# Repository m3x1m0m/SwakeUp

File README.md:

# SwakeUp
A device to wake you up in Sweden (because it is so dark in the winter).

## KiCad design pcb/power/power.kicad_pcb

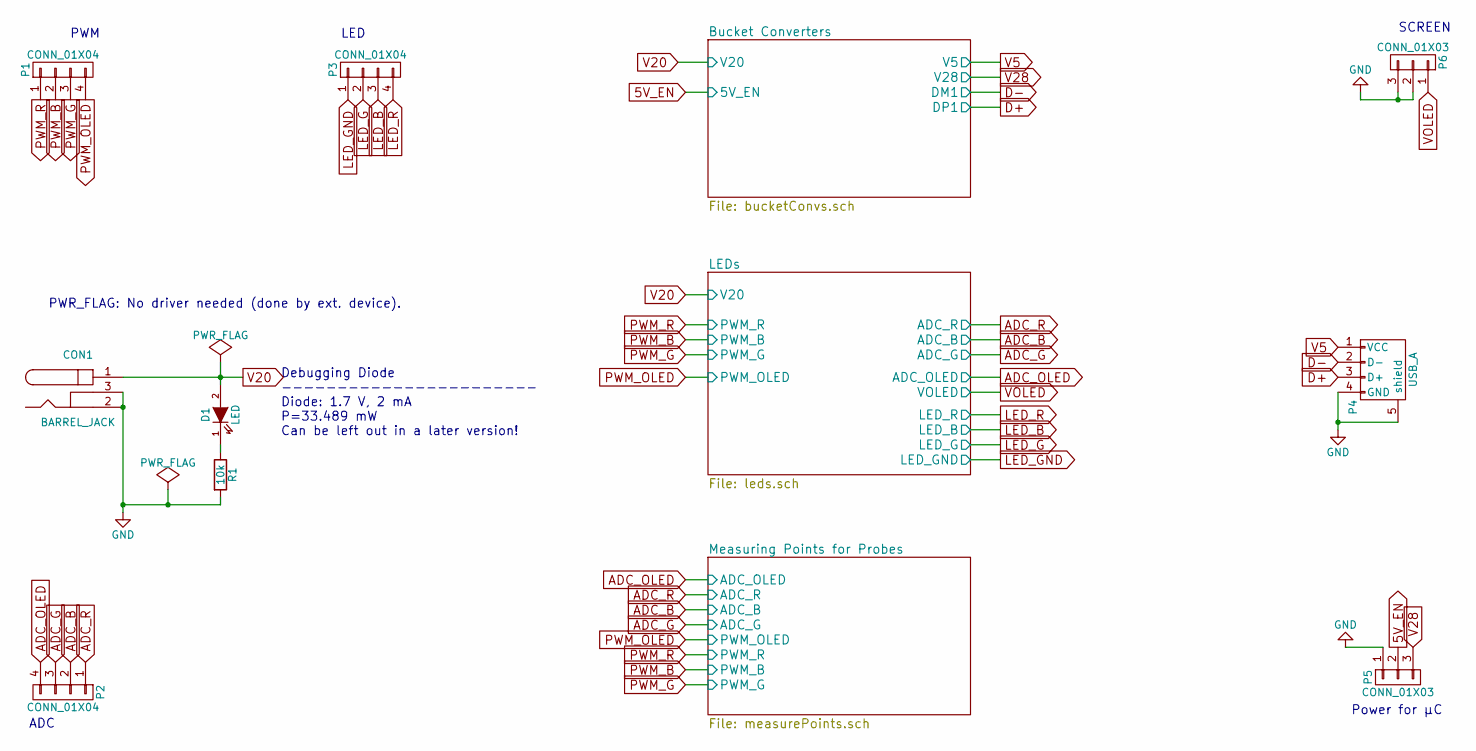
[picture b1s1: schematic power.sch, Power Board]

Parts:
CON1: BARREL_JACK; PJ-047BH_BARREL_JACK; Digikey CP-047BH-ND
D1: LED; LED_0603; Digikey 475-3118-1-ND
P1, P2: CONN_01X04; ESQ-104-12-G-S-LL
P3: CONN_01X04; LED_CONN_1.25_PITCH
P4: USB_A; Digikey 609-1045-ND
P5, P6: CONN_01X03; ESQ-103-12-G-S-LL
R1: 10k; R_0603_HandSoldering_Same_As_C; Digikey 311-10.0KHRCT-ND

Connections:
5V_EN: P5.2; also elsewhere on the board
ADC_B: P2.2; also elsewhere on the board
ADC_G: P2.3; also elsewhere on the board
ADC_OLED: P2.4; also elsewhere on the board
ADC_R: P2.1; also elsewhere on the board
D+: P4.3 (D+); also elsewhere on the board
D-: P4.2 (D-); also elsewhere on the board
LED_B: P3.2; also elsewhere on the board
LED_G: P3.3; also elsewhere on the board
LED_GND: CON1.2, CON1.3, P3.1, P4.4 (GND), P4.5 (shield), P5.1, P6.2, P6.3, R1.2; also elsewhere on the board
LED_R: P3.4; also elsewhere on the board
unnamed: D1.1 (K), R1.1
PWM_B: P1.2; also elsewhere on the board
PWM_G: P1.3; also elsewhere on the board
PWM_OLED: P1.4; also elsewhere on the board
PWM_R: P1.1; also elsewhere on the board
V5: P4.1 (VCC); also elsewhere on the board
V20: CON1.1, D1.2 (A); also elsewhere on the board
V28: P5.3; also elsewhere on the board
VOLED: P6.1; also elsewhere on the board

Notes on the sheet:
ADC
PWM
SCREEN
Debugging Diode ----------------------- Diode: 1.7 V, 2 mA P=33.489 mW Can be left out in a later version!
PWR_FLAG: No driver needed (done by ext. device).
Power for µC
LED

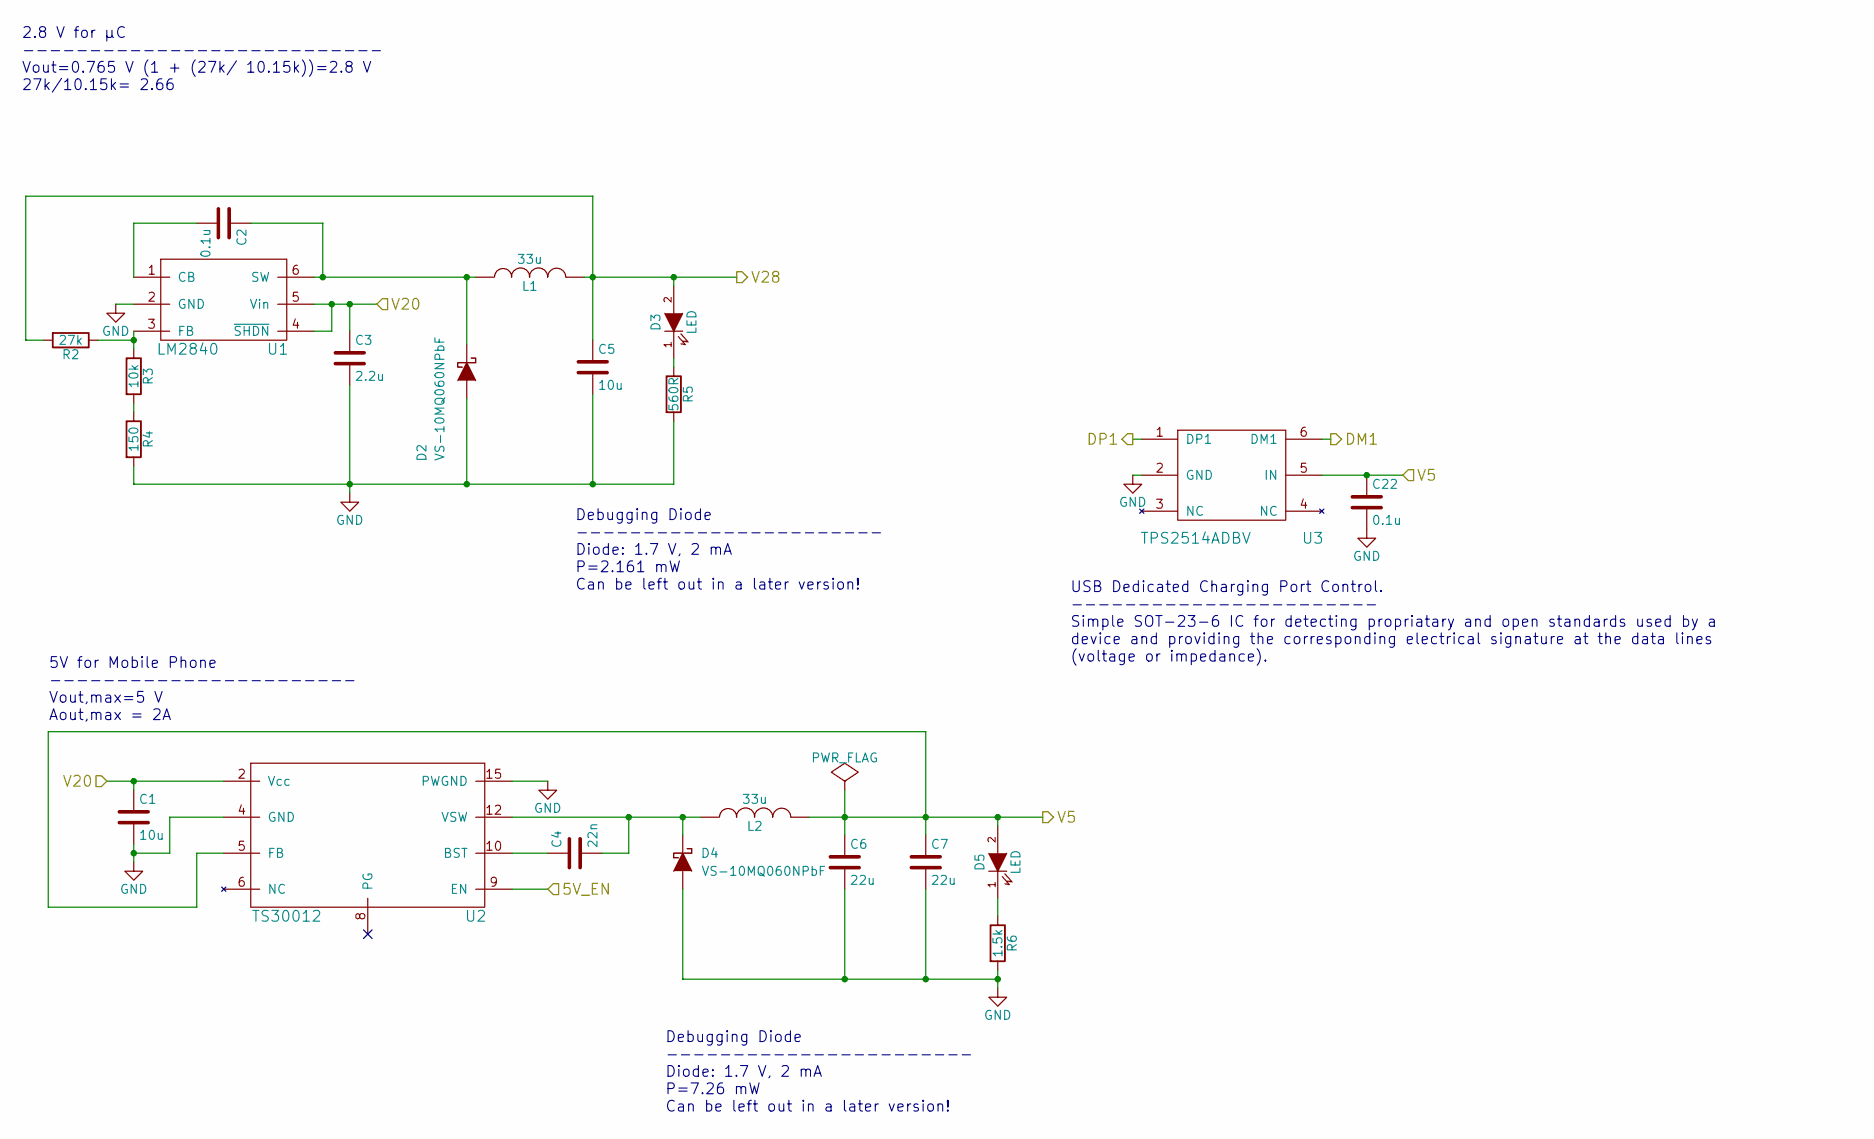
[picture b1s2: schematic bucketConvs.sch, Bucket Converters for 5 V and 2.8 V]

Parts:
C1, C5: 10u; C_0603_HandSoldering; Digikey 490-12323-1-ND
C2, C22: 0.1u; C_0603_HandSoldering; Digikey 311-1343-1-ND
C3: 2.2u; C_0603_HandSoldering; Digikey 490-7204-1-ND
C4: 22n; C_0603_HandSoldering; Digikey 445-8118-1-ND
C6, C7: 22u; C_0603_HandSoldering; Digikey 1276-1193-1-ND
D2, D4: VS-10MQ060NPbF; SMA_Handsoldering; Digikey 10MQ060NPBFCT-ND
D3, D5: LED; LED_0603; Digikey 475-3118-1-ND
L1, L2: 33u; Bourns_SRN3015; Digikey SRN3015-330MCT-ND
R2: 27k; R_0603_HandSoldering_Same_As_C; Digikey P27.0KHCT-ND
R3: 10k; R_0603_HandSoldering_Same_As_C; Digikey 311-10KGRCT-ND
R4: 150; R_0603_HandSoldering_Same_As_C; Digikey 311-150HRCT-ND
R5: 560R; R_0603_HandSoldering_Same_As_C; Digikey 311-560GRCT-ND
R6: 1.5k; R_0603_HandSoldering_Same_As_C; Digikey 311-1.5KGRCT-ND
U1: LM2840; SOT-23-6; Digikey LM2840XMK-ADJL/NOPBCT-ND
U2: TS30012; QFN-16-1EP_3x3mm_Pitch0.5mm; Digikey TS30012-M050QFNRCT-ND
U3: TPS2514ADBV; SOT-23-6; Digikey 296-40725-1-ND

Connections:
5V_EN: U2.9 (EN); also elsewhere on the board
D+: U3.1 (DP1); also elsewhere on the board
D-: U3.6 (DM1); also elsewhere on the board
LED_GND: C1.2, C3.2, C5.2, C6.2, C7.2, C22.2, D2.2 (A), D4.2 (A), R4.2, R5.2, R6.2, U1.2 (GND), U2.4 (GND), U2.14 (PWGND), U2.15 (PWGND), U3.2 (GND); also elsewhere on the board
unnamed: C2.1, D2.1 (K), L1.1, U1.6 (SW)
unnamed: C2.2, U1.1 (CB)
unnamed: C4.1, U2.10 (BST)
unnamed: C4.2, D4.1 (K), L2.1, U2.1 (VSW), U2.12 (VSW), U2.13 (VSW), U2.16 (VSW)
unnamed: D3.1 (K), R5.1
unnamed: D5.1 (K), R6.1
unnamed: R2.1, R3.1, U1.3 (FB)
unnamed: R3.2, R4.1
V5: C6.1, C7.1, C22.1, D5.2 (A), L2.2, U2.5 (FB), U3.5 (IN); also elsewhere on the board
V20: C1.1, C3.1, U1.4 (~SHDN), U1.5 (Vin), U2.2 (Vcc), U2.3 (Vcc), U2.11 (Vcc); also elsewhere on the board
V28: C5.1, D3.2 (A), L1.2, R2.2; also elsewhere on the board

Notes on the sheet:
2.8 V for µC --------------------------- Vout=0.765 V (1 + (27k/ 10.15k))=2.8 V 27k/10.15k= 2.66
Debugging Diode ----------------------- Diode: 1.7 V, 2 mA P=2.161 mW Can be left out in a later version!
Debugging Diode ----------------------- Diode: 1.7 V, 2 mA P=7.26 mW Can be left out in a later version!
5V for Mobile Phone ----------------------- Vout,max=5 V Aout,max = 2A
USB Dedicated Charging Port Control. ----------------------- Simple SOT-23-6 IC for detecting propriatary and open standards used by a device and providing the corresponding electrical signature at the data lines (voltage or impedance).

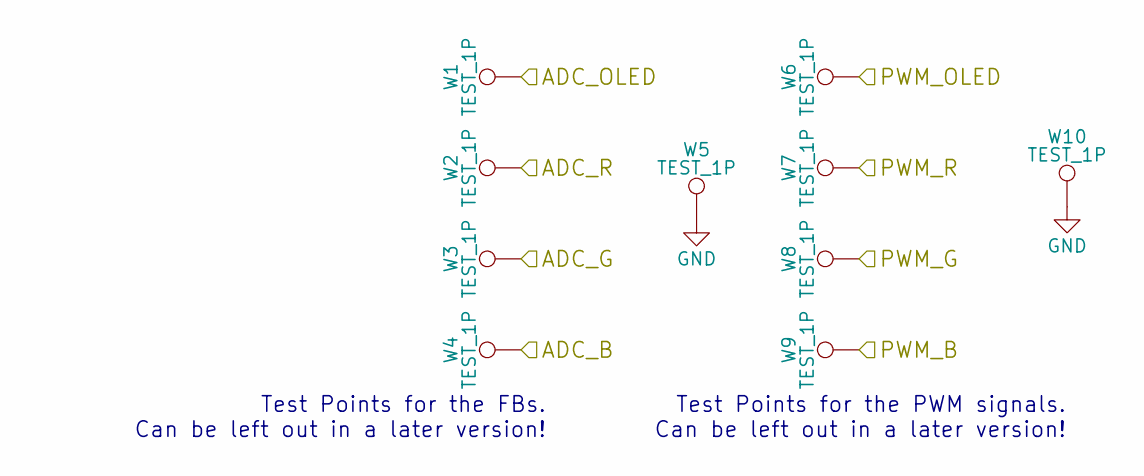
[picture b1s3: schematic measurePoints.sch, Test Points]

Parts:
W1, W2, W3, W4, W6, W7, W8, W9: TEST_1P; TP_PROBE
W5, W10: TEST_1P; GND_PROBE

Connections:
ADC_B: W4.1; also elsewhere on the board
ADC_G: W3.1; also elsewhere on the board
ADC_OLED: W1.1; also elsewhere on the board
ADC_R: W2.1; also elsewhere on the board
LED_GND: W5.1, W10.1; also elsewhere on the board
PWM_B: W9.1; also elsewhere on the board
PWM_G: W8.1; also elsewhere on the board
PWM_OLED: W6.1; also elsewhere on the board
PWM_R: W7.1; also elsewhere on the board

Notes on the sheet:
Test Points for the FBs. Can be left out in a later version!
Test Points for the PWM signals. Can be left out in a later version!

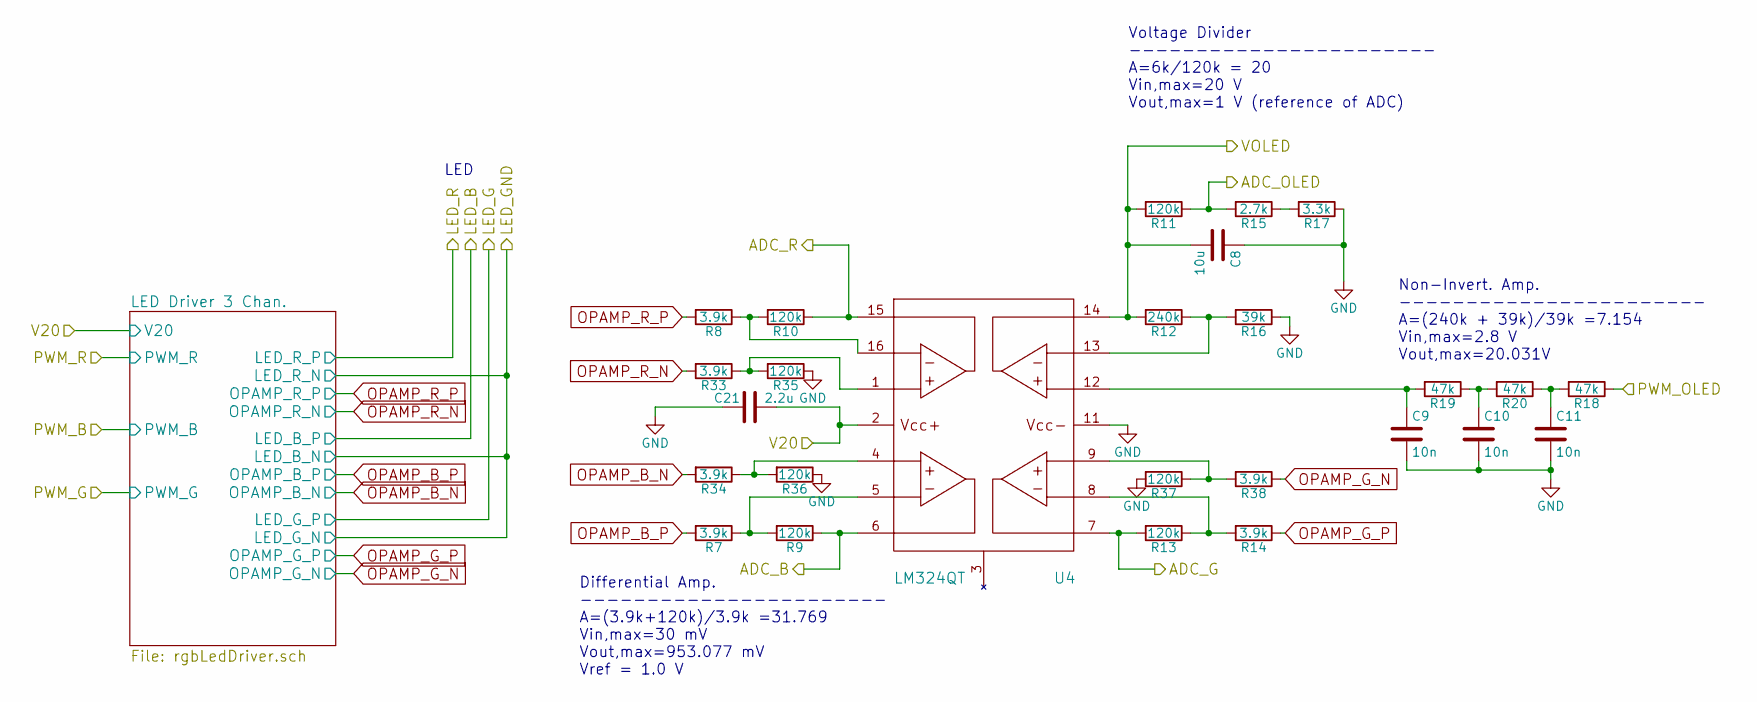
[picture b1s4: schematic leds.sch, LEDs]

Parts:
C8: 10u; C_0603_HandSoldering; Digikey 490-12323-1-ND
C9, C10, C11: 10n; C_0603_HandSoldering; Digikey 311-1085-1-ND
C21: 2.2u; C_0603_HandSoldering; Digikey 490-7204-1-ND
R7, R8, R14, R33, R34, R38: 3.9k; R_0603_HandSoldering_Same_As_C; Digikey 311-3.90KHRCT-ND
R9, R10, R11, R13, R35, R36, R37: 120k; R_0603_HandSoldering_Same_As_C; Digikey 311-120KHRCT-ND
R12: 240k; R_0603_HandSoldering_Same_As_C; Digikey 311-240KHRCT-ND
R15: 2.7k; R_0603_HandSoldering_Same_As_C; Digikey 311-2.70KHRCT-ND
R16: 39k; R_0603_HandSoldering_Same_As_C; Digikey 311-39.0KHRCT-ND
R17: 3.3k; R_0603_HandSoldering_Same_As_C; Digikey 311-3.30KHRCT-ND
R18, R19, R20: 47k; R_0603_HandSoldering_Same_As_C; Digikey 311-47.0KHRCT-ND
U4: LM324QT; QFN-16-1EP_3x3mm_Pitch0.5mm; Digikey 497-12005-1-ND

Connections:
ADC_B: R9.1, U4.6 (O_2); also elsewhere on the board
ADC_G: R13.2, U4.7 (O_3); also elsewhere on the board
ADC_OLED: R11.1, R15.2; also elsewhere on the board
ADC_R: R10.1, U4.15 (O_1); also elsewhere on the board
LED_B: R34.2; also elsewhere on the board
LED_G: R38.1; also elsewhere on the board
LED_GND: C8.1, C9.2, C10.2, C11.2, C21.1, R16.1, R17.1, R35.1, R36.1, R37.2, U4.11 (Vcc-); also elsewhere on the board
LED_R: R33.2; also elsewhere on the board
unnamed: C9.1, R19.2, U4.12 (P_4)
unnamed: C10.1, R19.1, R20.2
unnamed: C11.1, R18.2, R20.1
unnamed: R7.1, R9.2, U4.5 (N_2)
unnamed: R8.1, R10.2, U4.16 (N_1)
unnamed: R12.1, R16.2, U4.13 (N_4)
unnamed: R13.1, R14.2, U4.8 (N_3)
unnamed: R15.1, R17.2
unnamed: R33.1, R35.2, U4.1 (P_1)
unnamed: R34.1, R36.2, U4.4 (P_2)
unnamed: R37.1, R38.2, U4.9 (P_3)
OPAMP_B_P: R7.2; also elsewhere on the board
OPAMP_G_P: R14.1; also elsewhere on the board
OPAMP_R_P: R8.2; also elsewhere on the board
PWM_OLED: R18.1; also elsewhere on the board
V20: C21.2, U4.2 (Vcc+); also elsewhere on the board
VOLED: C8.2, R11.2, R12.2, U4.14 (O_4); also elsewhere on the board

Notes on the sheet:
Non-Invert. Amp. ----------------------- A=(240k + 39k)/39k =7.154 Vin,max=2.8 V Vout,max=20.031V
Differential Amp. ----------------------- A=(3.9k+120k)/3.9k =31.769 Vin,max=30 mV Vout,max=953.077 mV Vref = 1.0 V
Voltage Divider ----------------------- A=6k/120k = 20 Vin,max=20 V Vout,max=1 V (reference of ADC)
LED

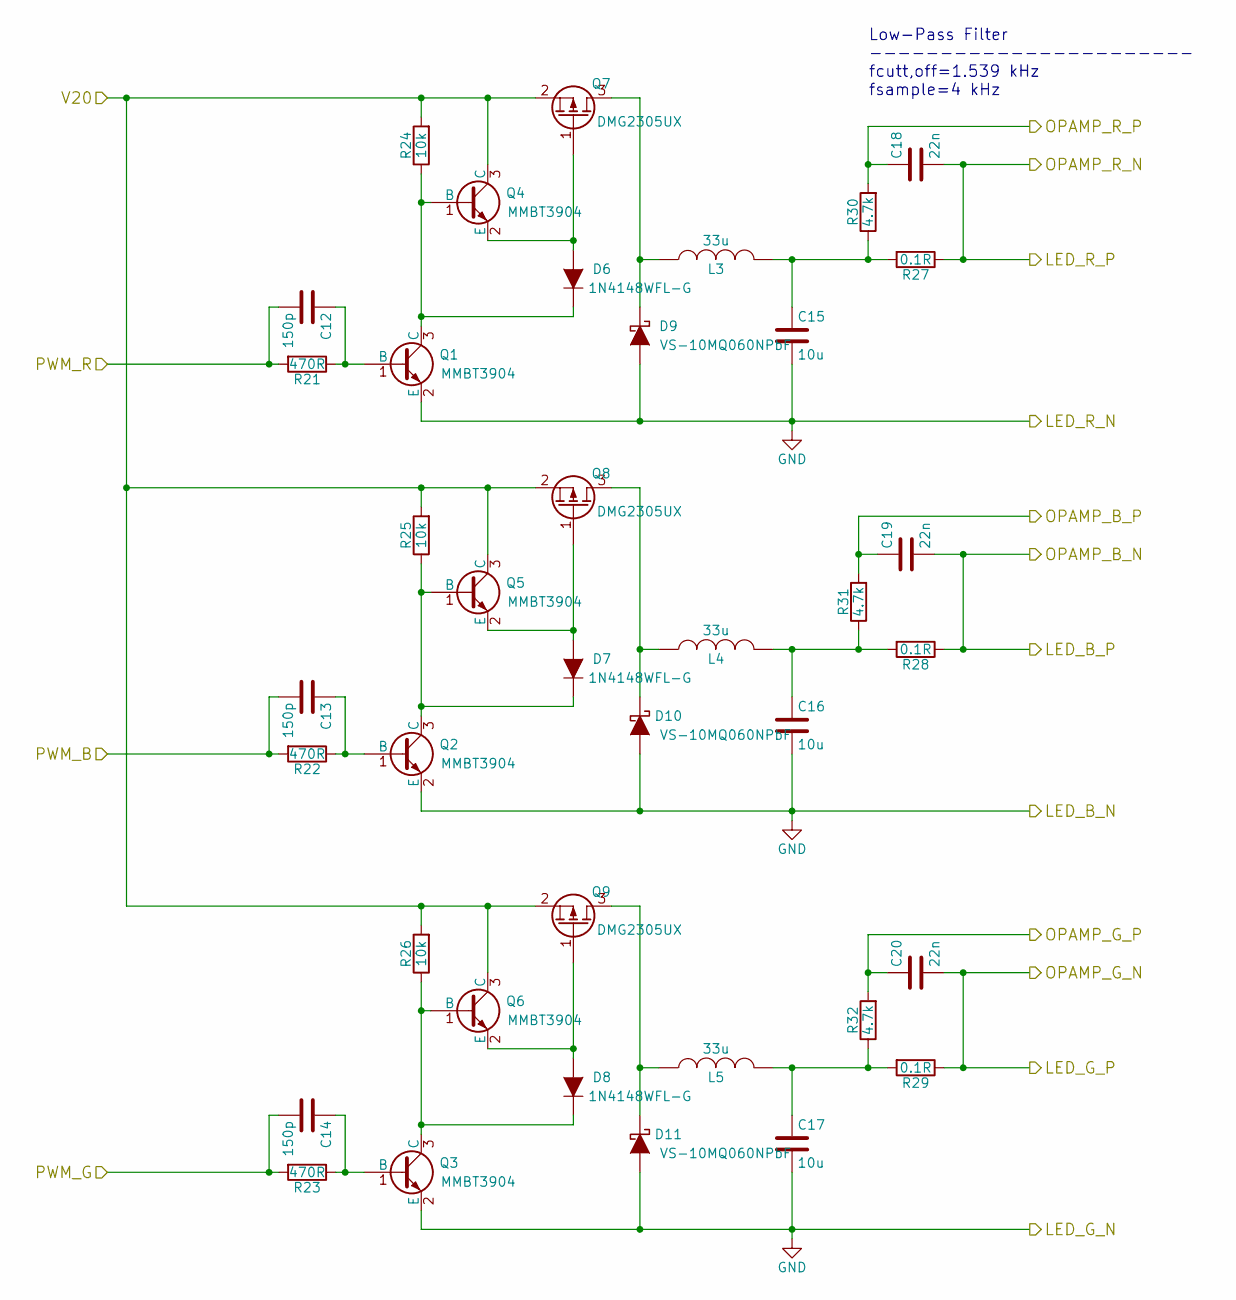
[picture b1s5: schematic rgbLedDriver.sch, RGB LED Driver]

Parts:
C12, C13, C14: 150p; C_0603_HandSoldering; Digikey 399-1063-1-ND
C15, C16, C17: 10u; C_0603_HandSoldering; Digikey 490-12323-1-ND
C18, C19, C20: 22n; C_0603_HandSoldering; Digikey 1276-1104-1-ND
D6, D7, D8: 1N4148WFL-G; SOD-123F; Farnell 1621821
D9, D10, D11: VS-10MQ060NPbF; SMA_Handsoldering; Digikey 10MQ060NPBFCT-ND
L3, L4, L5: 33u; Bourns_SRN3015; Digikey SRN3015-330MCT-ND
Q1, Q2, Q3, Q4, Q5, Q6: MMBT3904; SOT-23; Digikey MMBT3904TPMSCT-ND
Q7, Q8, Q9: DMG2305UX; SOT-23
R21, R22, R23: 470R; R_0603_HandSoldering_Same_As_C; Digikey 311-470HRCT-ND
R24, R25, R26: 10k; R_0603_HandSoldering_Same_As_C; Digikey 311-10KGRCT-ND
R27, R28, R29: 0.1R; R_0603_HandSoldering_Same_As_C; Digikey 1276-6155-1-ND
R30, R31, R32: 4.7k; R_0603_HandSoldering_Same_As_C; Digikey 311-4.7KGRCT-ND

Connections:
LED_B: C19.2, R28.1; also elsewhere on the board
LED_G: C20.2, R29.1; also elsewhere on the board
LED_GND: C15.2, C16.2, C17.2, D9.2 (A), D10.2 (A), D11.2 (A), Q1.2 (E), Q2.2 (E), Q3.2 (E); also elsewhere on the board
LED_R: C18.2, R27.1; also elsewhere on the board
unnamed: C12.1, Q1.1 (B), R21.1
unnamed: C13.1, Q2.1 (B), R22.1
unnamed: C14.1, Q3.1 (B), R23.1
unnamed: C15.1, L3.2, R27.2, R30.1
unnamed: C16.1, L4.2, R28.2, R31.1
unnamed: C17.1, L5.2, R29.2, R32.1
unnamed: D6.1 (K), Q1.3 (C), Q4.1 (B), R24.1
unnamed: D6.2 (A), Q4.2 (E), Q7.1 (G)
unnamed: D7.1 (K), Q2.3 (C), Q5.1 (B), R25.1
unnamed: D7.2 (A), Q5.2 (E), Q8.1 (G)
unnamed: D8.1 (K), Q3.3 (C), Q6.1 (B), R26.1
unnamed: D8.2 (A), Q6.2 (E), Q9.1 (G)
unnamed: D9.1 (K), L3.1, Q7.3 (D)
unnamed: D10.1 (K), L4.1, Q8.3 (D)
unnamed: D11.1 (K), L5.1, Q9.3 (D)
OPAMP_B_P: C19.1, R31.2; also elsewhere on the board
OPAMP_G_P: C20.1, R32.2; also elsewhere on the board
OPAMP_R_P: C18.1, R30.2; also elsewhere on the board
PWM_B: C13.2, R22.2; also elsewhere on the board
PWM_G: C14.2, R23.2; also elsewhere on the board
PWM_R: C12.2, R21.2; also elsewhere on the board
V20: Q4.3 (C), Q5.3 (C), Q6.3 (C), Q7.2 (S), Q8.2 (S), Q9.2 (S), R24.2, R25.2, R26.2; also elsewhere on the board

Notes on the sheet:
Low-Pass Filter ----------------------- fcutt,off=1.539 kHz fsample=4 kHz

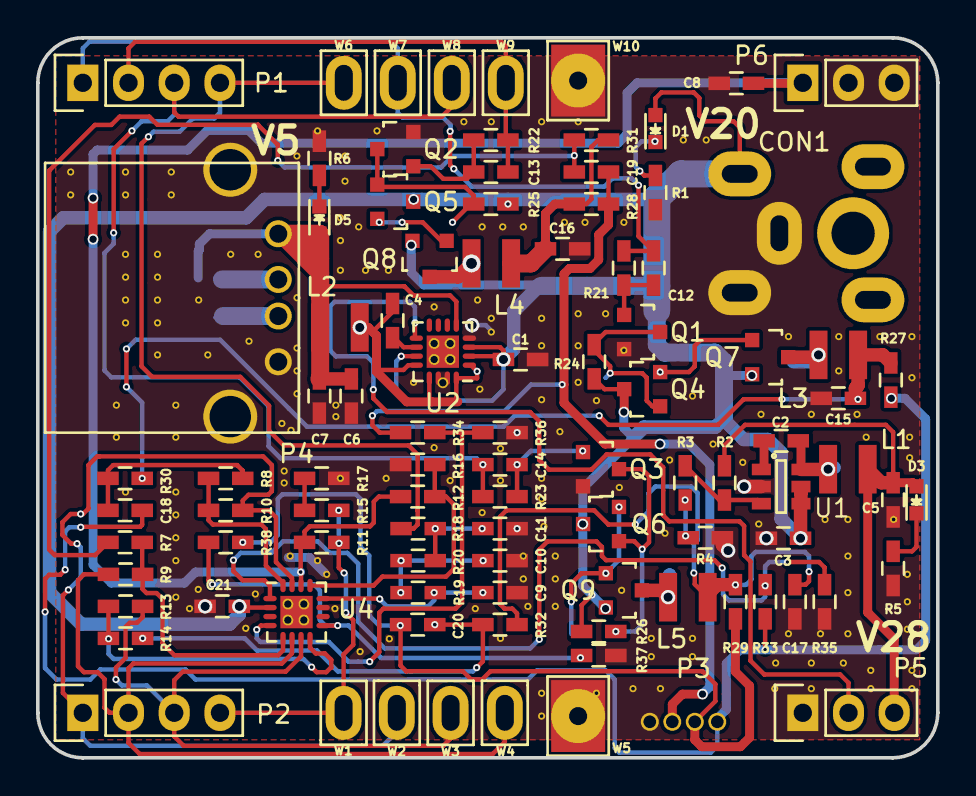
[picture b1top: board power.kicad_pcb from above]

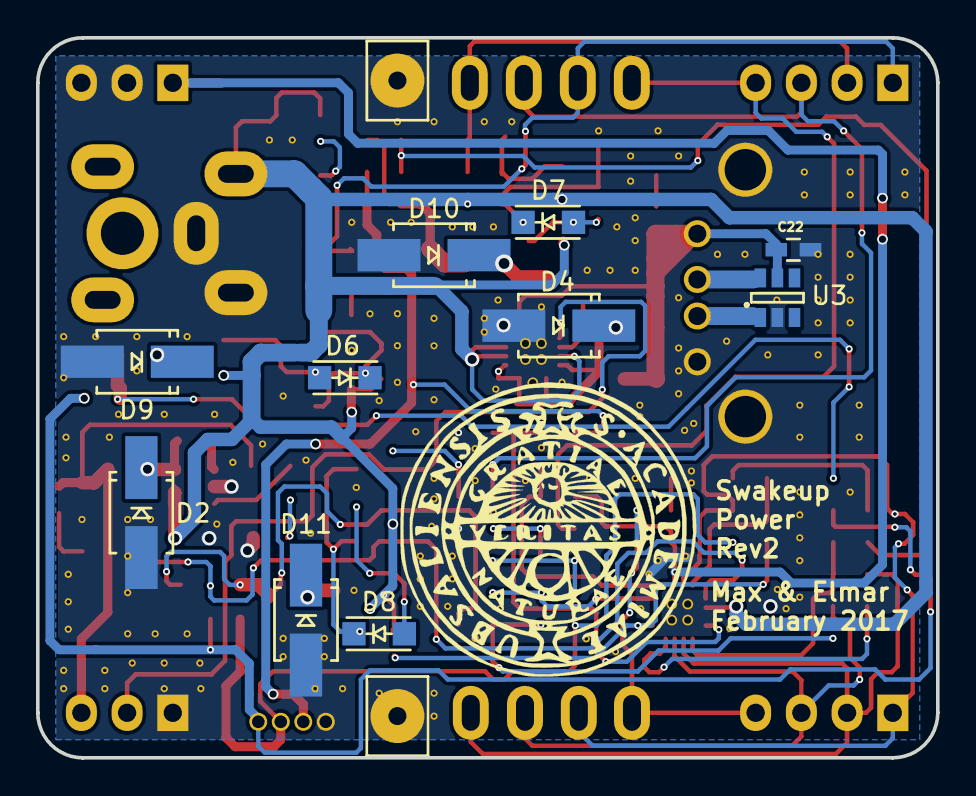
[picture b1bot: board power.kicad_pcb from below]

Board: 2 copper layers, 50.0 x 40.0 mm, 106 parts (10 on the bottom side), 57 nets.

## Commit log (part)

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2016-11-14 UART should work with interrupts now... should
2016-11-14 First module WIP
2016-11-14 migrating to a pin definitions file, much better
2016-11-14 getting there
2016-11-14 first commit of the timer, needs a lot of work. Is a 1 second timer now
2016-11-14 Fixed the event, also made UART a module
2016-11-14 nobody uses chars
2016-11-14 reworked the events, not using id's for comparisons anymore. Should also be faster
2016-11-14 Small example
2016-11-14 Added some datasheet.
2016-11-14 modified .gitignore again.
2016-11-14 Modified some smaller stuff.
2016-11-14 Fixed critical UART bug, now works on interrupt basis as well
2016-11-14 Started working on a PWM module.
2016-11-14 resolved a crash
2016-11-14 Removed some faulty code for now
2016-11-14 Logging is now in and functioning. Shows linenr + filename automatically. LOG_DEBUG("Test %d",123) works. Be sure to include LOG_INIT("Module name"); at the beginning of the c file though!
2016-11-14 Readme, so github will stop
2016-11-15 Uart is a little less static, works on 1,8 and 16 mHz. defaults to 9600 baud on 1, 38400 on 8 and 16
2016-11-17 Start with altium
2016-11-18 Schematics finished, general placement of components in design
2016-11-18 small
2016-11-18 Started with BOM. Added some datasheets.
2016-11-18 Edited blockdiagram. Seems to be in its final state now.
2016-11-18 Project settings
2016-11-18 Rev1 routed and finished
2016-11-21 Finalized PCB
2016-11-23 Forgot some minor routing. Hooked up some signals to vcc according to datasheet
2016-11-23 This really is important for the timer so that it can be used with different cpu frequencies
2016-11-24 Finished LED Driver.
2016-11-26 Did some simulation.
2016-11-26 Finished driver for 2.8 V.
2016-11-28 Finished almost everything in the schematic. Missing: Interfacing with elmare and the correct power connector for the 20 V power supply.
2016-11-28 Almost done with the schematics. Some fine tuning is left.
2016-12-01 Finished schematics.
2016-12-01 Worked on the Barrel Jack mainly, bought also a matching power supply. Nice!
2016-12-01 Added some more footprints. Maybe have to change some grounding stuff.
2016-12-02 Finished the schematics.
2016-12-02 Started layouting. Interfacing problems have to be discussed.
2016-12-11 Finished both bucket converters.
2016-12-23 Almost finished routing.
2016-12-24 Finished layout.
2016-12-26 Fnished board. Producing output now.
2016-12-26 Added some stitching vias.
2016-12-26 Only thing missing now in the 3D model is one diode type.
2016-12-30 Started completely over with the layout, as the OLED would not fit anymore. Also introduced a USB DCP Controller and found a stupid bug in the LED driver.
2016-12-30 Fixed the bug. Now workin with differential amplifiers. Started over once more with the layout.
2017-01-03 Finished rev 1 and generated gerber files.
2017-01-12 Finished up rev 1. Also added is a bom
2017-01-26 Gettin even with master.
2017-01-28 Organizing the PCB's
2017-01-29 Adjusted the RX and TX paths
2017-01-29 updated list of changes
2017-01-29 Stop generating rooms
2017-01-29 Proper main
2017-01-30 Making use of the RTC, not that efficient yet. But 1Hz works again
2017-01-30 Removed the led debug
2017-01-30 Start of REV version so old boards will keep working
2017-01-31 Not sure what this was doing here
2017-01-31 removed some garbage
2017-02-02 Warnings prevented
2017-02-02 Produced some output. Merge with master.
2017-02-07 ignore
2017-02-07 Working on event_wait
2017-02-07 Improved naming, removed redundant functions
2017-02-07 Sleep back in @ improved naming
2017-02-07 Reading back in, should test!!
2017-02-08 cleaned up a bit
2017-02-08 new command module, requires testing
2017-02-08 added single read, added more information to delimiter structure
2017-02-16 Some minor changes. Rev2 ready now.
2017-02-18 Produced some output. Soldermask changed: Less clearance.
2017-02-23 Start on the screen!
2017-02-23 Command + test case
2017-02-23 Screen is too broad, narrowed it down to the screen driver name. Also included <avr/io.h> not sure if this is a brilliant idea
2017-02-23 Added a lock while writing, prevents corruption. Removed some arguments. Solved a bug with the reading of data
2017-02-23 Adjusted to work with the new uart.h
2017-02-24 Screen driver seems to work so far, still needs performance adjustments
2017-02-24 Callbacks should be static!
2017-02-25 Renamed variable, removed warning
2017-02-25 Added a greeting, TODO get actual time removed warning added AT test command
2017-02-26 Font is in, and a test image
2017-02-26 Added a sink, and a timer during debug (seconds, should become miliseconds)
2017-02-26 Added a few drawing functions which makes some performance boost possible
2017-02-26 Testing out with the new log
2017-02-26 To work with the log sink
2017-02-26 Added const and solved simple bug
2017-02-26 request current sink
2017-02-26 Still working and failling on interrupt based spi
2017-02-26 Prevented warning
2017-02-26 Testing out the screen
2017-02-27 REV2
2017-02-27 Now we can see which commands are registered with '?'
2017-02-28 small mistake
2017-02-28 We can receive ESP messages now! Investigate crash upon /r/n
2017-02-28 Stops the system upon error
2017-02-28 ESP writing data :)
2017-03-01 Memory usage from 45% -> 23%
2017-03-01 Clock functionality
2017-03-01 Lets see some weather!
2017-03-01 More advanced command options
2017-03-02 Fixed the log routine and added functions for reading of flash
2017-03-02 Fixed drawing sub image, fixed drawing text
2017-03-03 Shows alarm now. thats pretty cool
2017-03-03 Abstracting the time keeping
2017-03-03 We can now parse integers
2017-03-03 Moved logic to the core. Code is slowly getting clean
2017-03-03 We can now request some status. Setting time works
2017-03-03 Fixed some typos
2017-03-03 Moved some stuff to defines, now we don't have to edit the main file anymore
2017-03-06 Cleaned a bit and added a report.
2017-03-06 Whoops. Forgot to track a directory.
2017-03-07 Reduction of warnings
2017-03-07 This should be used soon
2017-03-08 start of presentation. Powerpoint. Sorry max
2017-03-09 Switching from screen terminal to uart terminal works now. Setting time reflects to the clock app.
2017-03-09 Weird bug with drawing text
2017-03-09 Came quite far with the report.
2017-03-09 Added the appendix and continued on the realization
2017-03-09 realization finished
2017-03-09 Added source
2017-03-09 Finished my part of the report rougly. Adding pictures.
2017-03-09 Finalized logic explanation. Its terrible
2017-03-10 Added a bibliography.
2017-03-10 report rev 1
2017-03-14 Trying to figure out a coloured drawing function
2017-03-22 Presentation.
2017-03-25 Start of esp project
2017-03-26 To be programmed
2017-03-26 gitignore
2017-04-13 REV 2 support
2017-04-13 Cleaned up a bit.
2017-04-24 Moved stuff around
2017-04-24 Control system in place, we can now send and receive protobuf messages. Requires a lot of testing
2017-04-24 Processing the messages, should be able to update time and weather. TODO naming convention
2017-04-25 protobuf start
2017-04-25 Moved the cpu to the defines
2017-04-25 proto messages should be handled over event, need flags to see if msgframe is available!
2017-04-25 Moved logging initialization
2017-04-26 Debugging, and omitted a crash
2017-04-26 Proto test
2017-04-27 typo
2017-04-27 More indepht information for the UART streams
2017-04-27 nanopb, this is needed. Sorry for the binaries
2017-04-27 Proposel document
2017-04-27 numbers used on screen
2017-04-27 updated gitignore for latex
2017-04-27 User input does not get erased anymore after enter. Started on interpreting arrow keys + tab. Strange behavior
2017-04-29 Adjusted bat file, generates for ESP, Xmega and backend
2017-04-29 added the esp project
2017-05-01 start of wifi stream
2017-05-01 utils to simulate the get requests from esp
2017-05-01 restful stream implementation. should send post to server with protobuf
2017-05-03 Rest stream almost working, server backend receiving empty payload
2017-05-03 Workaround for the max outgoing stream size, should be added to constructor maybe
2017-05-04 At last its possible to send and receive messages successfully
2017-05-04 disabled for testing
2017-05-04 Minor changes.
2017-05-04 Fixed fro Eclipse.
2017-05-04 Started with the PWM.
2017-05-04 Tried to get PWM working. Does not work yet.
2017-05-04 updated definitions
2017-05-05 renamed the old date and location to one unit
2017-05-05 Wrote a nice function for setting freq. Maybe a bit of an overkill here.
2017-05-05 All PWM channels working. Terminal interaction possible. Need to fix some smaller things.
2017-05-08 Garbage cleanup
2017-05-08 Refactored slightly
2017-05-08 Preparation for complete xmega integration
2017-05-08 Have to figure out where to place these
2017-05-08 Moved the location, as its needed for almost everything requested
2017-05-08 Updated backend, now can request time and weather updated on location
2017-05-08 xmega integration
2017-05-08 This should be generated
2017-05-08 Working example of the message deligator
2017-05-09 pdf for rev2
2017-05-10 Simulations.
2017-05-11 Moved pin definitions. Started with PID.
2017-05-11 Fixed PID problem.
2017-05-11 Updated the weather to reflect the new protobuf files
2017-05-11 Updated the Weather and time to reflect the new protobuf files
2017-05-11 Updated with location and celcius
2017-05-11 Altium adjustments
2017-05-11 This should not be pushed
2017-05-11 Moved some code that should not have been where it was
2017-05-12 Important fix for the screen
2017-05-12 Almost finished the new schematics.
2017-05-13 omitted a warning
2017-05-13 Added features, set what to display globally, set what to debug locally
2017-05-13 Required for the new logging
2017-05-13 Small typo, fixed AM PM
2017-05-13 Rewrote the clock, now works with new timekeeper module. Also shows date. No more analogue clock
2017-05-13 moved sprites to a sepperate file
2017-05-13 Added debug possibility
2017-05-13 UI V2, now contains a status bar and mail interface
2017-05-13 only update when really needed
2017-05-14 Slightly longer city/country names
2017-05-14 updated to work with newest proto files
2017-05-14 Dont process errorous messages
2017-05-14 added doxygen output
2017-05-14 Should not be drawing if not enabled. Mail app has stackoverflow hidden!!
2017-05-14 Bytes seem to work easier than strings, slightly more code overhead
2017-05-14 Test with weather, also updated for newest protobuf
2017-05-15 Got ADC up and running interupt based.
2017-05-15 Made ADC code more elegant (shorted LOCs).
2017-05-15 experimental 32mHz support, for screen refresh
2017-05-15 gitignores
2017-05-16 Started with the PID.
2017-05-16 Fixed the console to work after disabling it again
2017-05-17 Declared operations on fixed points as static inline.
2017-05-18 Got REV1 working. Dirty fix, which needs to be improved.
2017-05-18 Part of the webserver integrated, city can now be set via web browser
2017-05-21 Updated with new site layout, TODO: add the alarm list
2017-05-23 PID infrastructure works.
2017-05-23 Made my stuff running again after epic merge.
2017-05-24 Wrote a module for light pattern. Moved PID in the module dir.
2017-05-24 Added a simple alarm module. Fixed some stuff in the lightcnt.
2017-05-25 We need at least one main
2017-05-25 Cleaned SPI
2017-05-25 I like this gitignore more
2017-05-26 Optimized PWM module a lot.
2017-05-31 Added PID script and curves.
2017-05-31 Added a Makefile for the report.
2017-05-31 Strcutured report roughly.
2017-05-31 Updated the esp files to reflect the website better
2017-05-31 Finer structure.
2017-05-31 Finished design.
2017-05-31 Start on the backend documentation
2017-05-31 Started with evaluation part.
2017-05-31 Back from gym.
2017-05-31 Finished HW description.
2017-05-31 Added a newer schematics version.
2017-05-31 Added figures and written implementations/logic board
2017-05-31 website
2017-05-31 \cite not \ref
2017-05-31 wrong reference
2017-05-31 reference
2017-06-01 Lightcontroller works 90%. Need merge.
2017-06-01 Elmar changed smth. here. IDK.
2017-06-01 Cleaning.
2017-06-01 Presentation finished.
